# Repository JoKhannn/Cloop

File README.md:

# Stomper

**IN DEVELOPEMENT** <br /> 
Stepper driver designed to be mounted on bottom of motors. Daisy chainable CAN BUS and power delivery. Closed loop encoder.

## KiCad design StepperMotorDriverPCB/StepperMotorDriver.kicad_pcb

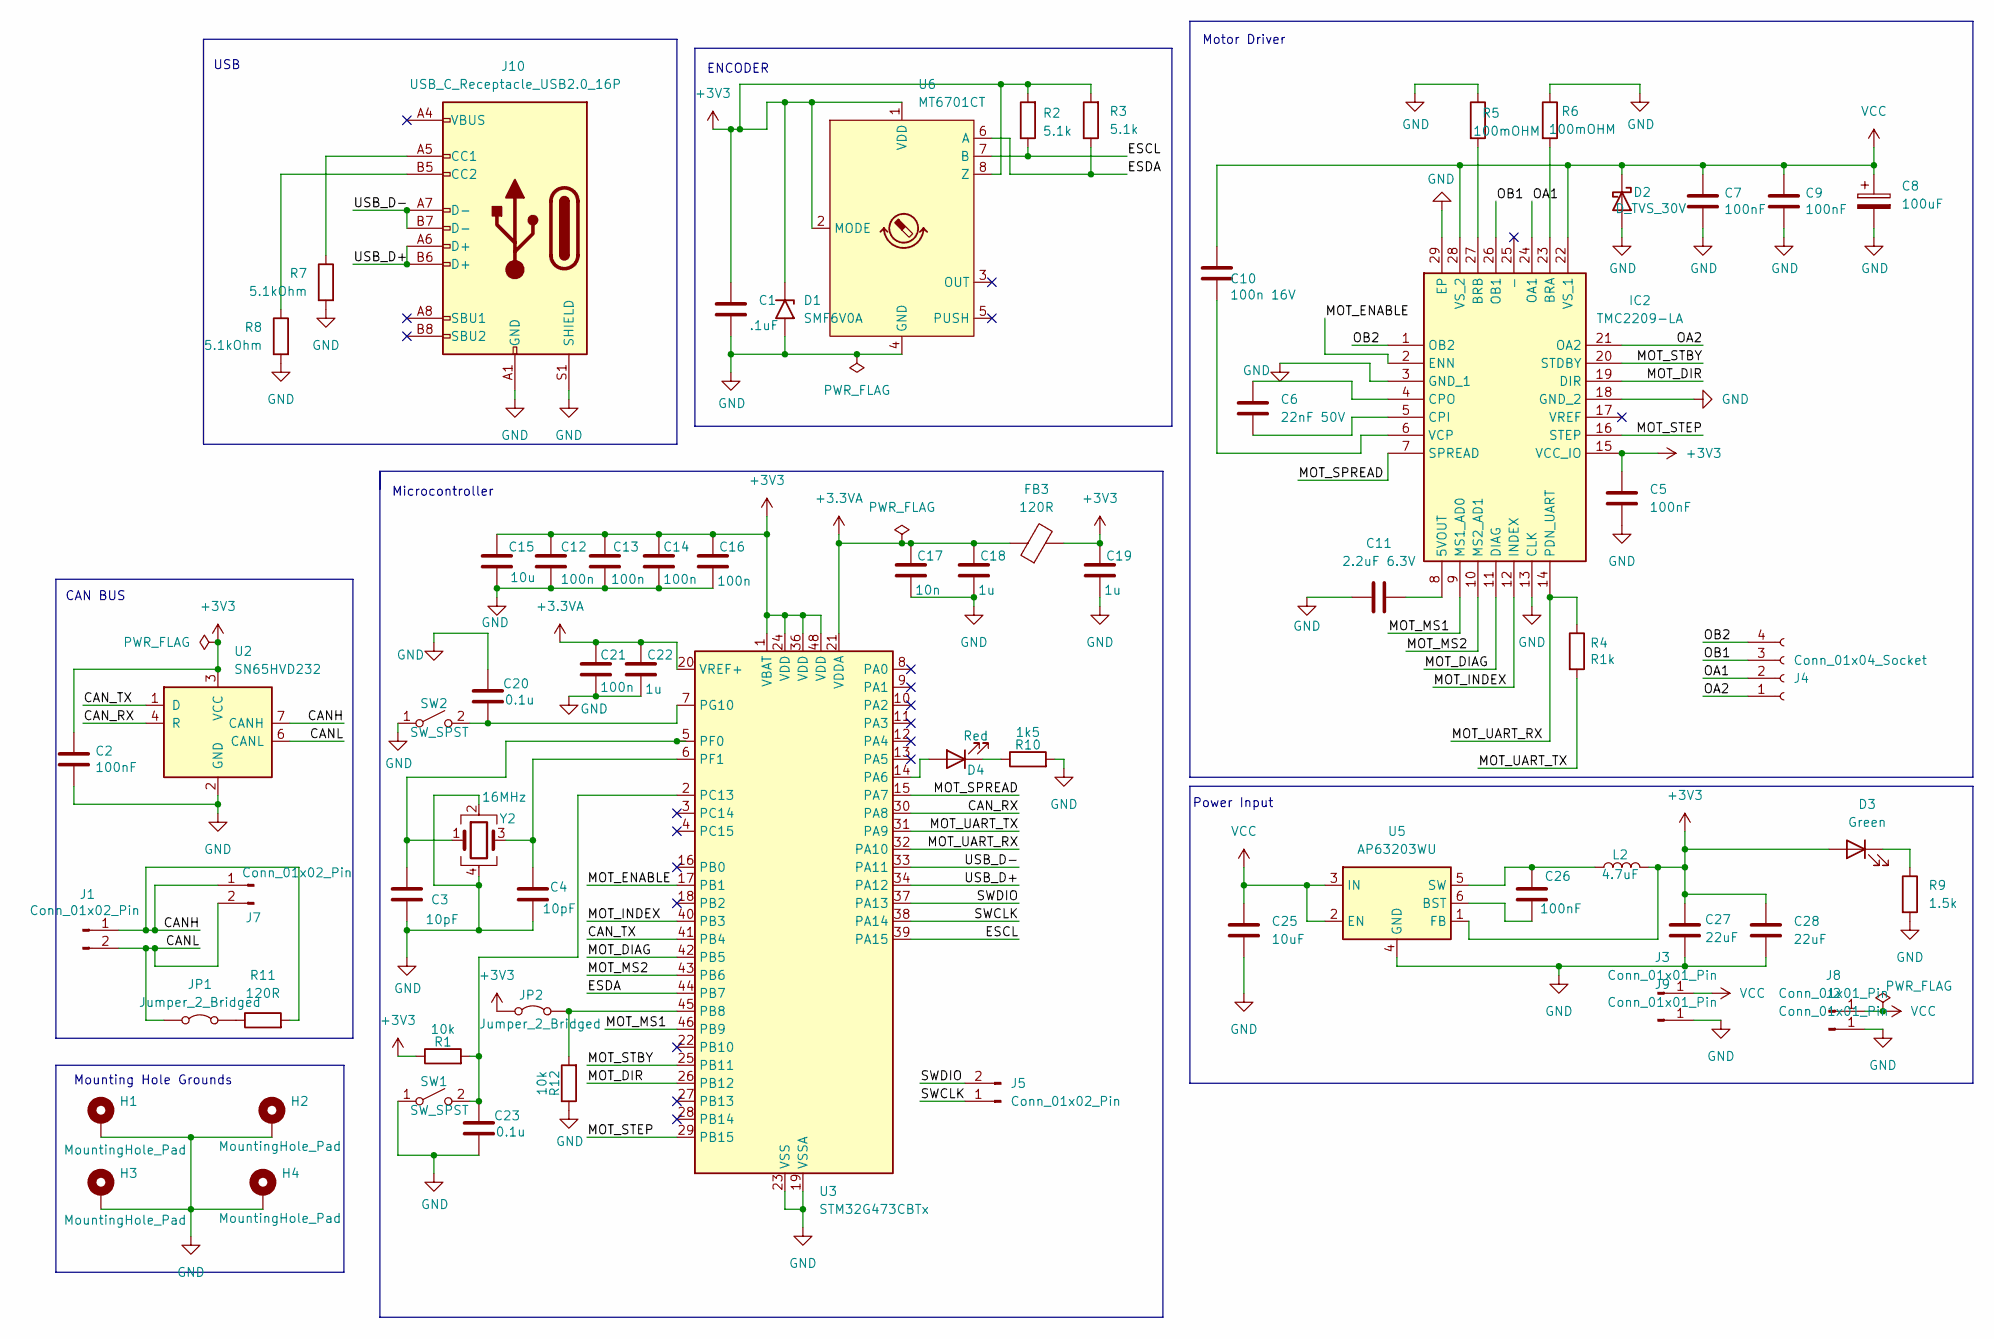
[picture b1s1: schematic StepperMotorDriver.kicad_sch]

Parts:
C1: .1uF; C_0402_1005Metric
C2, C7: 100nF; C_0402_1005Metric; LCSC C13585
C3, C4: 10pF; C_0402_1005Metric
C5, C26: 100nF; C_0402_1005Metric
C6: 22nF 50V; C_0402_1005Metric
C8: 100uF; CP_Radial_D5.0mm_P2.50mm
C9: 100nF; C_0402_1005Metric; LCSC C14663
C10: 100n 16V; C_0603_1608Metric
C11: 2.2uF 6.3V; C_0603_1608Metric
C12, C13, C14, C16, C21: 100n; C_0402_1005Metric
C15: 10u; C_0603_1608Metric
C17: 10n; C_0402_1005Metric
C18, C19, C22: 1u; C_0402_1005Metric
C20, C23: 0.1u; C_0402_1005Metric
C25: 10uF; C_0603_1608Metric
C27, C28: 22uF; C_0805_2012Metric
D1: SMF6V0A; D_SMF
D2: D_TVS_30V; D_0603_1608Metric; LCSC C553410
D3: Green; LED_0603_1608Metric
D4: Red; LED_0603_1608Metric
FB3: 120R; L_0603_1608Metric
H1, H2, H3, H4: MountingHole_Pad; MountingHole_3.2mm_M3_DIN965_Pad
IC2: TMC2209-LA; QFN50P500X500X90-29N; Mouser Part Number 700-TMC2209-LA
J1, J7: Conn_01x02_Pin; JST_XH_S2B-XH-A-1_1x02_P2.50mm_Horizontal
J2, J3, J8, J9: Conn_01x01_Pin; TestPoint_Plated_Hole_D2.0mm
J4: Conn_01x04_Socket; JST_XH_S4B-XH-A-1_1x04_P2.50mm_Horizontal
J5: Conn_01x02_Pin; PinHeader_1x02_P2.00mm_Vertical
J10: USB_C_Receptacle_USB2.0_16P; USB_C_Receptacle_Palconn_UTC16-G
JP1, JP2: Jumper_2_Bridged; SolderJumper-2_P1.3mm_Open_RoundedPad1.0x1.5mm
L2: 4.7uF; L_Chilisin_BMRA00050530
R1, R12: 10k; R_0402_1005Metric
R2, R3: 5.1k; R_0402_1005Metric
R4: R1k; R_0402_1005Metric; LCSC C11702
R5, R6: 100mOHM; R_1206_3216Metric
R7, R8: 5.1kOhm; R_0402_1005Metric
R9: 1.5k; R_0402_1005Metric
R10: 1k5; R_0402_1005Metric
R11: 120R; R_0402_1005Metric
SW1, SW2: SW_SPST; SW_PUSH_1P1T_6x3.5mm_H5.0_APEM_MJTP1250
U2: SN65HVD232; SOIC-8_3.9x4.9mm_P1.27mm
U3: STM32G473CBTx; LQFP-48_7x7mm_P0.5mm
U5: AP63203WU; TSOT-23-6
U6: MT6701CT; SO-8_3.9x4.9mm_P1.27mm
Y2: 16MHz; Crystal_SMD_3225-4Pin_3.2x2.5mm

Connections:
+3.3VA: C17.1, C18.1, C21.1, C22.1, FB3.1, U3.20 (VREF+), U3.21 (VDDA)
+3V3: C1.1, C2.1, C5.1, C12.1, C13.1, C14.1, C15.1, C16.1, C19.1, C27.1, C28.2, D1.1 (A1), D3.2 (A), FB3.2, IC2.15 (VCC_IO), JP2.1 (A), L2.2, R1.1, R2.2, R3.2, U2.3 (VCC), U3.1 (VBAT), U3.24 (VDD), U3.36 (VDD), U3.48 (VDD), U5.1 (FB), U6.1 (VDD), U6.2 (MODE), U6.8 (Z)
/CANH: J1.1, J7.1, R11.2, U2.7 (CANH)
/CANL: J1.2, J7.2, JP1.1 (A), U2.6 (CANL)
/CAN_RX: U2.4 (R), U3.30 (PA8)
/CAN_TX: U2.1 (D), U3.41 (PB4)
/ESCL: R2.1, U3.39 (PA15), U6.7 (B)
/ESDA: R3.1, U3.44 (PB7), U6.6 (A)
/MOT_DIAG: IC2.11 (DIAG), U3.42 (PB5)
/MOT_DIR: IC2.19 (DIR), U3.26 (PB12)
/MOT_ENABLE: IC2.2 (ENN), U3.17 (PB1)
/MOT_INDEX: IC2.12 (INDEX), U3.40 (PB3)
/MOT_MS1: IC2.9 (MS1_AD0), U3.46 (PB9)
/MOT_MS2: IC2.10 (MS2_AD1), U3.43 (PB6)
/MOT_SPREAD: IC2.7 (SPREAD), U3.15 (PA7)
/MOT_STBY: IC2.20 (STDBY), U3.25 (PB11)
/MOT_STEP: IC2.16 (STEP), U3.29 (PB15)
/MOT_UART_RX: IC2.14 (PDN_UART), R4.1, U3.32 (PA10)
/MOT_UART_TX: R4.2, U3.31 (PA9)
/OA1: IC2.24 (OA1), J4.2
/OA2: IC2.21 (OA2), J4.1
/OB1: IC2.26 (OB1), J4.3
/OB2: IC2.1 (OB2), J4.4
/SWCLK: J5.1, U3.38 (PA14)
/SWDIO: J5.2, U3.37 (PA13)
/USB_D+: J10.A6 (D+), J10.B6 (D+), U3.34 (PA12)
/USB_D-: J10.A7 (D-), J10.B7 (D-), U3.33 (PA11)
GND: C1.2, C2.2, C3.2, C4.2, C5.2, C7.2, C8.2, C9.2, C11.1, C12.2, C13.2, C14.2, C15.2, C16.2, C17.2, C18.2, C19.2, C20.1, C21.2, C22.2, C23.2, C25.1, C27.2, C28.1, D1.2 (A2), D2.2 (A), H1.1, H2.1, H3.1, H4.1, IC2.3 (GND_1), IC2.13 (CLK), IC2.18 (GND_2), IC2.29 (EP), J2.1, J9.1, J10.A1 (GND), J10.A12 (GND), J10.B1 (GND), J10.B12 (GND), J10.S1 (SHIELD), R5.1, R6.1, R7.2, R8.2, R9.2, R10.2, R12.1, SW1.1 (A), SW2.1 (A), U2.2 (GND), U3.19 (VSSA), U3.23 (VSS), U3.35 (VSS), U3.47 (VSS), U5.4 (GND), U6.4 (GND), Y2.2, Y2.4
unnamed: D3.1 (K), R9.1
unnamed: D4.2 (A), U3.14 (PA6)
unnamed: D4.1 (K), R10.1
unnamed: C11.2, IC2.8 (5VOUT)
unnamed: IC2.23 (BRA), R6.2
unnamed: IC2.27 (BRB), R5.2
unnamed: C6.2, IC2.5 (CPI)
unnamed: C6.1, IC2.4 (CPO)
unnamed: C10.2, IC2.6 (VCP)
unnamed: J10.A5 (CC1), R7.1
unnamed: J10.B5 (CC2), R8.1
unnamed: JP1.2 (B), R11.1
unnamed: JP2.2 (B), R12.2, U3.45 (PB8)
unnamed: C23.1, R1.2, SW1.2 (B), U3.2 (PC13)
unnamed: C20.2, SW2.2 (B), U3.7 (PG10)
unnamed: C3.1, U3.5 (PF0), Y2.1
unnamed: C4.1, U3.6 (PF1), Y2.3
unnamed: C26.2, U5.6 (BST)
unnamed: C26.1, L2.1, U5.5 (SW)
VCC: C7.1, C8.1, C9.1, C10.1, C25.2, D2.1 (K), IC2.22 (VS_1), IC2.28 (VS_2), J3.1, J8.1, U5.2 (EN), U5.3 (IN)

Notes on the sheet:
CAN BUS
Power Input
ENCODER
Microcontroller
Mounting Hole Grounds
USB
Motor Driver

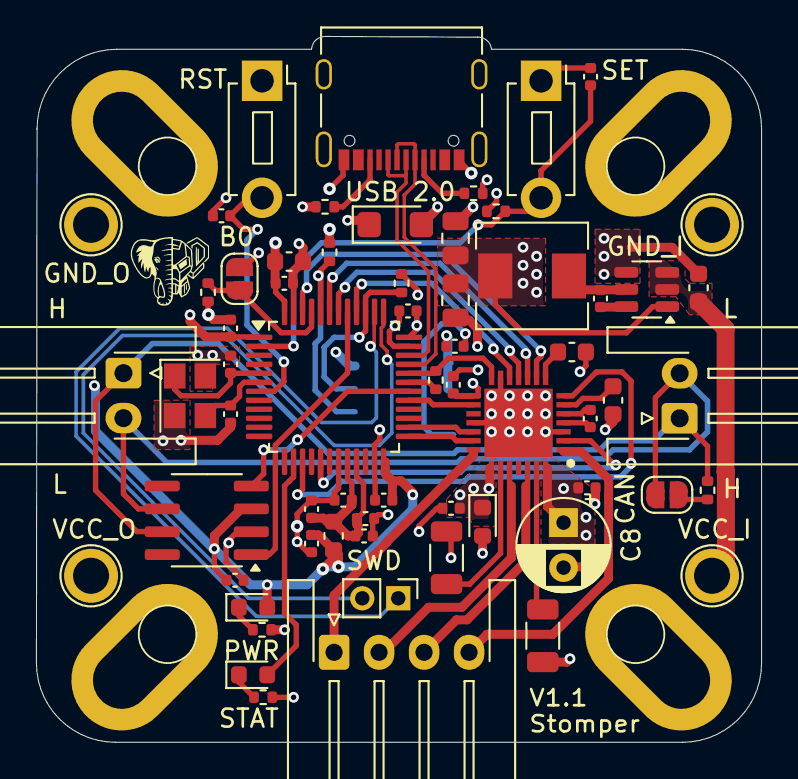
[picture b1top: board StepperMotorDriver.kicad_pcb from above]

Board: 4 copper layers, 40.3 x 39.2 mm, 68 parts (1 on the bottom side), 48 nets.

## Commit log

2024-07-18 Create placeholder
2024-07-18 Adding Files
2024-08-12 Replaced Microcontrollers and Power Distribution System
2024-08-12 Adjusted CAN passthroughh
2024-08-28 Major changes to layout
    Made everything but encoder on top layer. Changed to stronger MC, new buttons, etc.
2024-08-30 Major Structural Updates.
    Updated mounting hardware and PD
2024-09-16 Updates to circuitry
2024-09-17 Minor routing adjustment.
